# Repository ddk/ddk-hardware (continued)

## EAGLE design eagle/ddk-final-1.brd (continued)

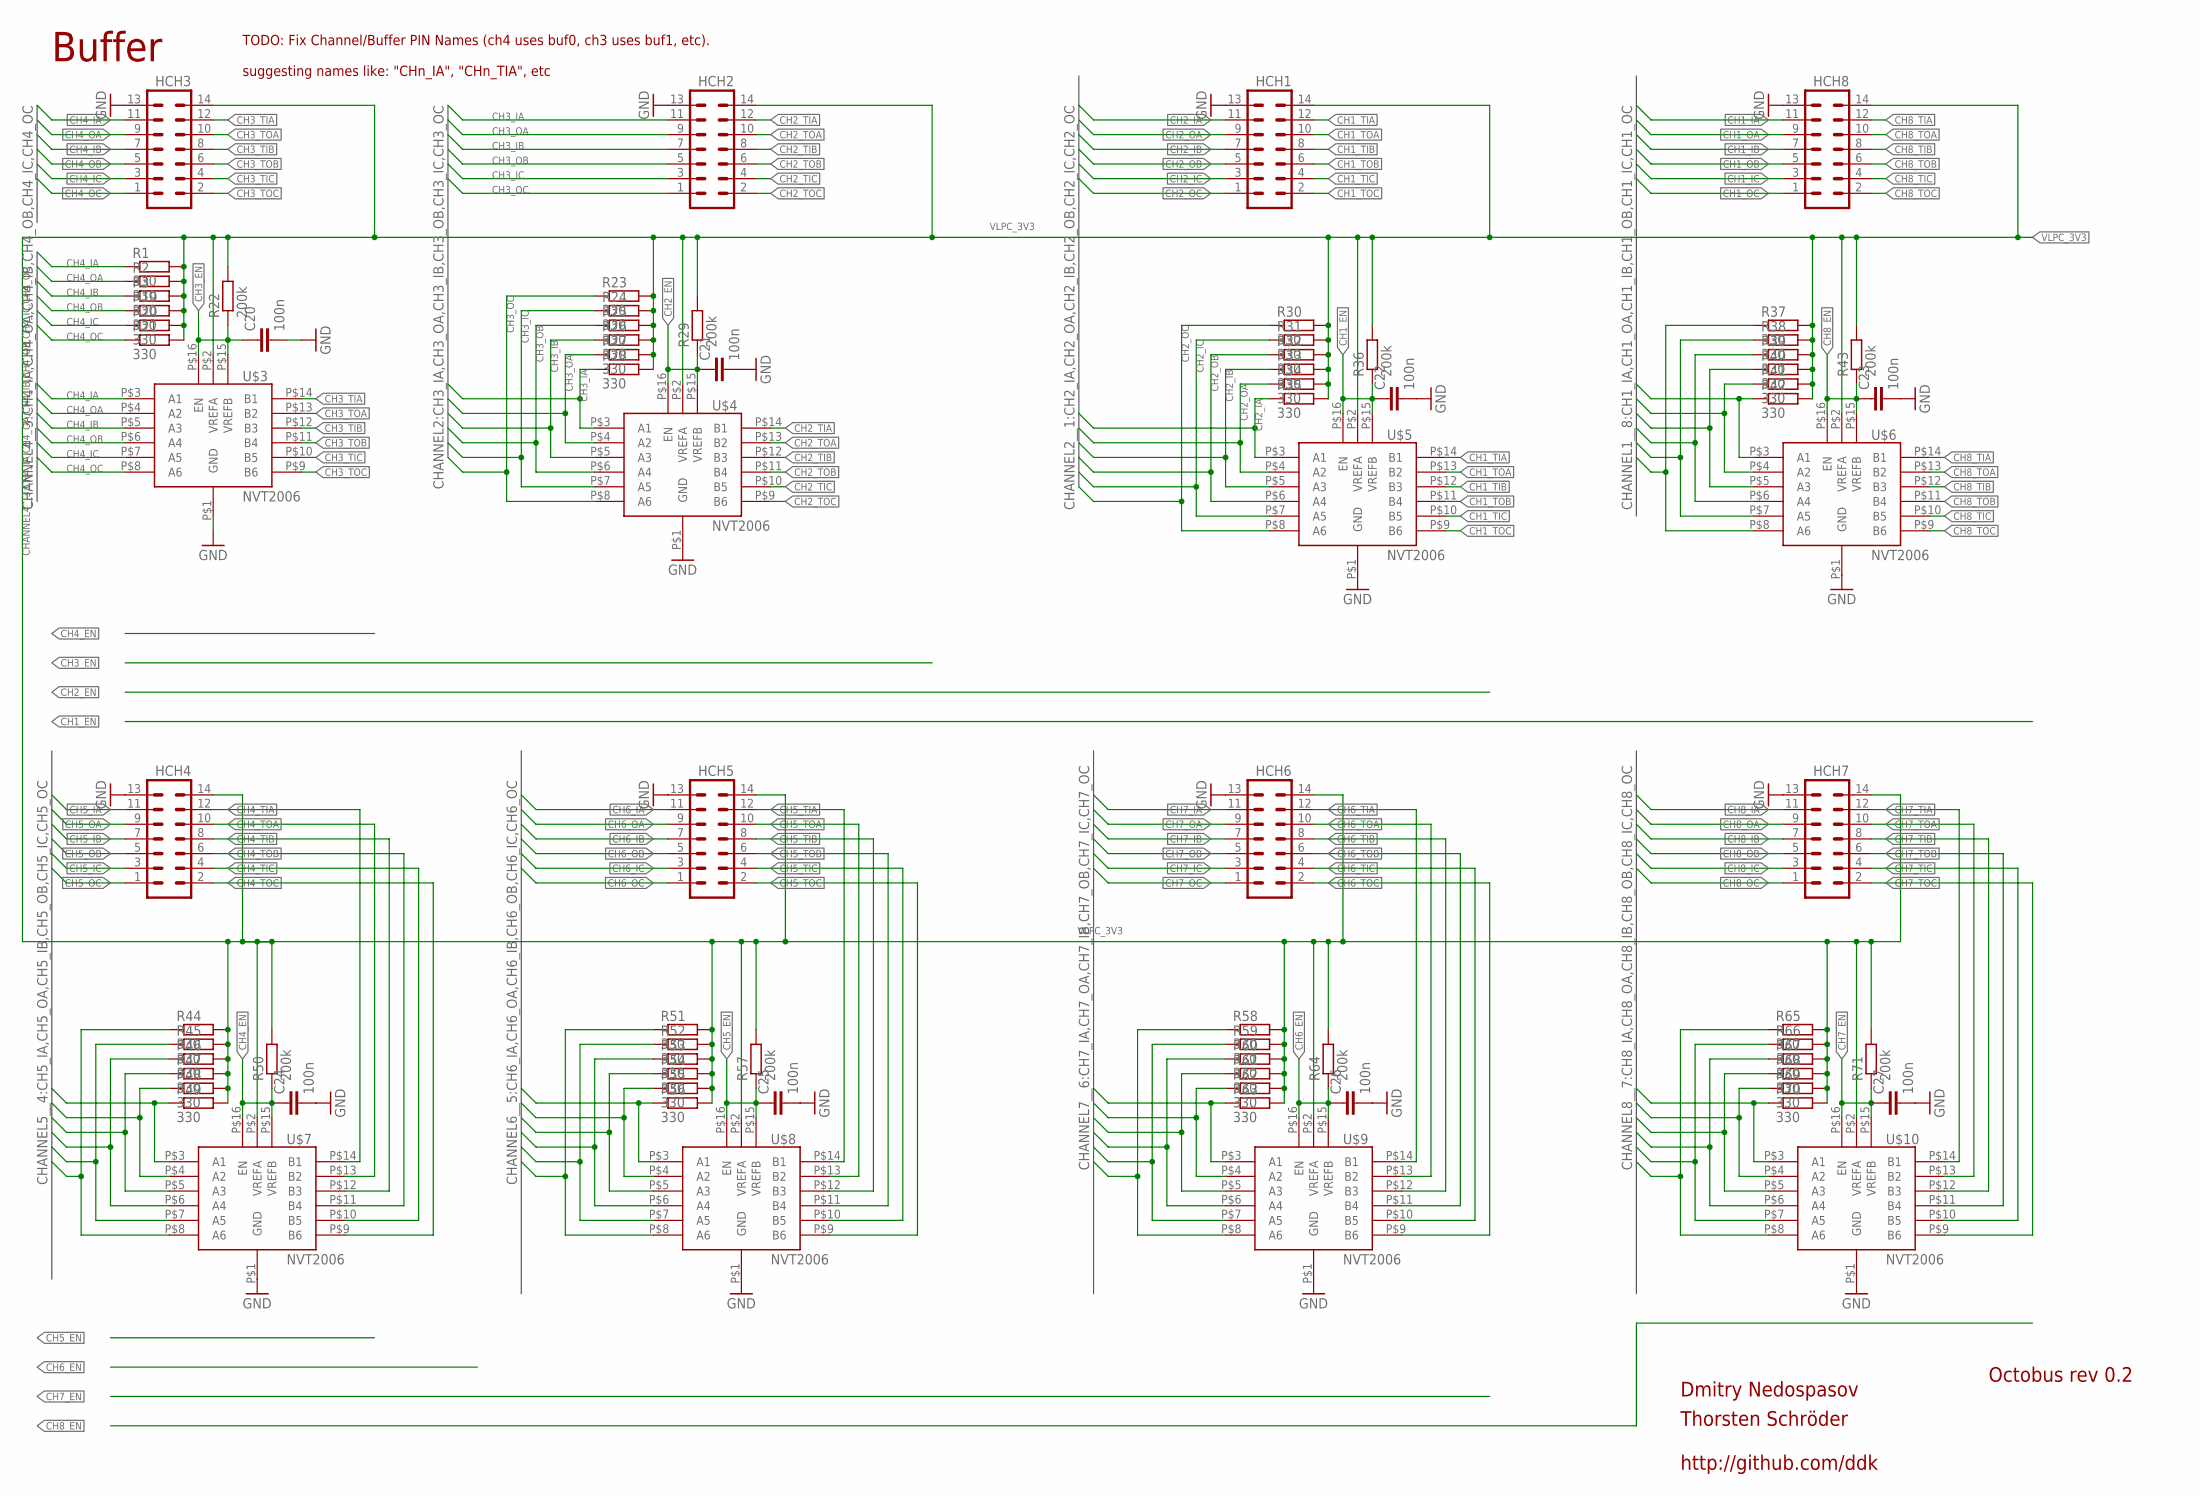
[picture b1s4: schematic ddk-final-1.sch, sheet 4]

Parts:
C20, C21, C22, C23, C24, C25, C26, C27: 100n; C0603
HCH1, HCH2, HCH3, HCH4, HCH5, HCH6, HCH7, HCH8: MA07-2
R1, R2, R3, R19, R20, R21, R23, R24, R25, R26, R27, R28, R30, R31, R32, R33, R34, R35, R37, R38, R39, R40, R41, R42, R44, R45, R46, R47, R48, R49, R51, R52, R53, R54, R55, R56, R58, R59, R60, R61, R62, R63, R65, R66, R67, R68, R69, R70: 330; R0603
R22, R29, R36, R43, R50, R57, R64, R71: 200k; R0603
U$3, U$4, U$5, U$6, U$7, U$8, U$9, U$10: NVT2006; TSSOP16

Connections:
CH1_EN: C22.1, R36.1, U$5.P$15 (VREFB), U$5.P$16 (EN); also elsewhere on the board
CH1_IA: HCH8.11, R42.1, U$6.P$3 (A1); also elsewhere on the board
CH1_IB: HCH8.7, R40.1, U$6.P$5 (A3); also elsewhere on the board
CH1_IC: HCH8.3, R38.1, U$6.P$7 (A5); also elsewhere on the board
CH1_OA: HCH8.9, R41.1, U$6.P$4 (A2); also elsewhere on the board
CH1_OB: HCH8.5, R39.1, U$6.P$6 (A4); also elsewhere on the board
CH1_OC: HCH8.1, R37.1, U$6.P$8 (A6); also elsewhere on the board
CH1_TIA: HCH1.12, U$5.P$14 (B1); also elsewhere on the board
CH1_TIB: HCH1.8, U$5.P$12 (B3); also elsewhere on the board
CH1_TIC: HCH1.4, U$5.P$10 (B5); also elsewhere on the board
CH1_TOA: HCH1.10, U$5.P$13 (B2); also elsewhere on the board
CH1_TOB: HCH1.6, U$5.P$11 (B4); also elsewhere on the board
CH1_TOC: HCH1.2, U$5.P$9 (B6); also elsewhere on the board
CH2_EN: C21.1, R29.1, U$4.P$15 (VREFB), U$4.P$16 (EN); also elsewhere on the board
CH2_IA: HCH1.11, R35.1, U$5.P$3 (A1); also elsewhere on the board
CH2_IB: HCH1.7, R33.1, U$5.P$5 (A3); also elsewhere on the board
CH2_IC: HCH1.3, R31.1, U$5.P$7 (A5); also elsewhere on the board
CH2_OA: HCH1.9, R34.1, U$5.P$4 (A2); also elsewhere on the board
CH2_OB: HCH1.5, R32.1, U$5.P$6 (A4); also elsewhere on the board
CH2_OC: HCH1.1, R30.1, U$5.P$8 (A6); also elsewhere on the board
CH2_TIA: HCH2.12, U$4.P$14 (B1); also elsewhere on the board
CH2_TIB: HCH2.8, U$4.P$12 (B3); also elsewhere on the board
CH2_TIC: HCH2.4, U$4.P$10 (B5); also elsewhere on the board
CH2_TOA: HCH2.10, U$4.P$13 (B2); also elsewhere on the board
CH2_TOB: HCH2.6, U$4.P$11 (B4); also elsewhere on the board
CH2_TOC: HCH2.2, U$4.P$9 (B6); also elsewhere on the board
CH3_EN: C20.1, R22.1, U$3.P$15 (VREFB), U$3.P$16 (EN); also elsewhere on the board
CH3_IA: HCH2.11, R28.1, U$4.P$3 (A1); also elsewhere on the board
CH3_IB: HCH2.7, R26.1, U$4.P$5 (A3); also elsewhere on the board
CH3_IC: HCH2.3, R24.1, U$4.P$7 (A5); also elsewhere on the board
CH3_OA: HCH2.9, R27.1, U$4.P$4 (A2); also elsewhere on the board
CH3_OB: HCH2.5, R25.1, U$4.P$6 (A4); also elsewhere on the board
CH3_OC: HCH2.1, R23.1, U$4.P$8 (A6); also elsewhere on the board
CH3_TIA: HCH3.12, U$3.P$14 (B1); also elsewhere on the board
CH3_TIB: HCH3.8, U$3.P$12 (B3); also elsewhere on the board
CH3_TIC: HCH3.4, U$3.P$10 (B5); also elsewhere on the board
CH3_TOA: HCH3.10, U$3.P$13 (B2); also elsewhere on the board
CH3_TOB: HCH3.6, U$3.P$11 (B4); also elsewhere on the board
CH3_TOC: HCH3.2, U$3.P$9 (B6); also elsewhere on the board
CH4_EN: C24.1, R50.1, U$7.P$15 (VREFB), U$7.P$16 (EN); also elsewhere on the board
CH4_IA: HCH3.11, R1.1, U$3.P$3 (A1); also elsewhere on the board
CH4_IB: HCH3.7, R3.1, U$3.P$5 (A3); also elsewhere on the board
CH4_IC: HCH3.3, R20.1, U$3.P$7 (A5); also elsewhere on the board
CH4_OA: HCH3.9, R2.1, U$3.P$4 (A2); also elsewhere on the board
CH4_OB: HCH3.5, R19.1, U$3.P$6 (A4); also elsewhere on the board
CH4_OC: HCH3.1, R21.1, U$3.P$8 (A6); also elsewhere on the board
CH4_TIA: HCH4.12, U$7.P$14 (B1); also elsewhere on the board
CH4_TIB: HCH4.8, U$7.P$12 (B3); also elsewhere on the board
CH4_TIC: HCH4.4, U$7.P$10 (B5); also elsewhere on the board
CH4_TOA: HCH4.10, U$7.P$13 (B2); also elsewhere on the board
CH4_TOB: HCH4.6, U$7.P$11 (B4); also elsewhere on the board
CH4_TOC: HCH4.2, U$7.P$9 (B6); also elsewhere on the board
CH5_EN: C25.1, R57.1, U$8.P$15 (VREFB), U$8.P$16 (EN); also elsewhere on the board
CH5_IA: HCH4.11, R49.1, U$7.P$3 (A1); also elsewhere on the board
CH5_IB: HCH4.7, R47.1, U$7.P$5 (A3); also elsewhere on the board
CH5_IC: HCH4.3, R45.1, U$7.P$7 (A5); also elsewhere on the board
CH5_OA: HCH4.9, R48.1, U$7.P$4 (A2); also elsewhere on the board
CH5_OB: HCH4.5, R46.1, U$7.P$6 (A4); also elsewhere on the board
CH5_OC: HCH4.1, R44.1, U$7.P$8 (A6); also elsewhere on the board
CH5_TIA: HCH5.12, U$8.P$14 (B1); also elsewhere on the board
CH5_TIB: HCH5.8, U$8.P$12 (B3); also elsewhere on the board
CH5_TIC: HCH5.4, U$8.P$10 (B5); also elsewhere on the board
CH5_TOA: HCH5.10, U$8.P$13 (B2); also elsewhere on the board
CH5_TOB: HCH5.6, U$8.P$11 (B4); also elsewhere on the board
CH5_TOC: HCH5.2, U$8.P$9 (B6); also elsewhere on the board
CH6_EN: C26.1, R64.1, U$9.P$15 (VREFB), U$9.P$16 (EN); also elsewhere on the board
CH6_IA: HCH5.11, R56.1, U$8.P$3 (A1); also elsewhere on the board
CH6_IB: HCH5.7, R54.1, U$8.P$5 (A3); also elsewhere on the board
CH6_IC: HCH5.3, R52.1, U$8.P$7 (A5); also elsewhere on the board
CH6_OA: HCH5.9, R55.1, U$8.P$4 (A2); also elsewhere on the board
CH6_OB: HCH5.5, R53.1, U$8.P$6 (A4); also elsewhere on the board
CH6_OC: HCH5.1, R51.1, U$8.P$8 (A6); also elsewhere on the board
CH6_TIA: HCH6.12, U$9.P$14 (B1); also elsewhere on the board
CH6_TIB: HCH6.8, U$9.P$12 (B3); also elsewhere on the board
CH6_TIC: HCH6.4, U$9.P$10 (B5); also elsewhere on the board
CH6_TOA: HCH6.10, U$9.P$13 (B2); also elsewhere on the board
CH6_TOB: HCH6.6, U$9.P$11 (B4); also elsewhere on the board
CH6_TOC: HCH6.2, U$9.P$9 (B6); also elsewhere on the board
CH7_EN: C27.1, R71.1, U$10.P$15 (VREFB), U$10.P$16 (EN); also elsewhere on the board
CH7_IA: HCH6.11, R63.1, U$9.P$3 (A1); also elsewhere on the board
CH7_IB: HCH6.7, R61.1, U$9.P$5 (A3); also elsewhere on the board
CH7_IC: HCH6.3, R59.1, U$9.P$7 (A5); also elsewhere on the board
CH7_OA: HCH6.9, R62.1, U$9.P$4 (A2); also elsewhere on the board
CH7_OB: HCH6.5, R60.1, U$9.P$6 (A4); also elsewhere on the board
CH7_OC: HCH6.1, R58.1, U$9.P$8 (A6); also elsewhere on the board
CH7_TIA: HCH7.12, U$10.P$14 (B1); also elsewhere on the board
CH7_TIB: HCH7.8, U$10.P$12 (B3); also elsewhere on the board
CH7_TIC: HCH7.4, U$10.P$10 (B5); also elsewhere on the board
CH7_TOA: HCH7.10, U$10.P$13 (B2); also elsewhere on the board
CH7_TOB: HCH7.6, U$10.P$11 (B4); also elsewhere on the board
CH7_TOC: HCH7.2, U$10.P$9 (B6); also elsewhere on the board
CH8_EN: C23.1, R43.1, U$6.P$15 (VREFB), U$6.P$16 (EN); also elsewhere on the board
CH8_IA: HCH7.11, R70.1, U$10.P$3 (A1); also elsewhere on the board
CH8_IB: HCH7.7, R68.1, U$10.P$5 (A3); also elsewhere on the board
CH8_IC: HCH7.3, R66.1, U$10.P$7 (A5); also elsewhere on the board
CH8_OA: HCH7.9, R69.1, U$10.P$4 (A2); also elsewhere on the board
CH8_OB: HCH7.5, R67.1, U$10.P$6 (A4); also elsewhere on the board
CH8_OC: HCH7.1, R65.1, U$10.P$8 (A6); also elsewhere on the board
CH8_TIA: HCH8.12, U$6.P$14 (B1); also elsewhere on the board
CH8_TIB: HCH8.8, U$6.P$12 (B3); also elsewhere on the board
CH8_TIC: HCH8.4, U$6.P$10 (B5); also elsewhere on the board
CH8_TOA: HCH8.10, U$6.P$13 (B2); also elsewhere on the board
CH8_TOB: HCH8.6, U$6.P$11 (B4); also elsewhere on the board
CH8_TOC: HCH8.2, U$6.P$9 (B6); also elsewhere on the board
GND: C20.2, C21.2, C22.2, C23.2, C24.2, C25.2, C26.2, C27.2, HCH1.13, HCH2.13, HCH3.13, HCH4.13, HCH5.13, HCH6.13, HCH7.13, HCH8.13, U$3.P$1 (GND), U$4.P$1 (GND), U$5.P$1 (GND), U$6.P$1 (GND), U$7.P$1 (GND), U$8.P$1 (GND), U$9.P$1 (GND), U$10.P$1 (GND); also elsewhere on the board
VLPC_3V3: HCH1.14, HCH2.14, HCH3.14, HCH4.14, HCH5.14, HCH6.14, HCH7.14, HCH8.14, R1.2, R2.2, R3.2, R19.2, R20.2, R21.2, R22.2, R23.2, R24.2, R25.2, R26.2, R27.2, R28.2, R29.2, R30.2, R31.2, R32.2, R33.2, R34.2, R35.2, R36.2, R37.2, R38.2, R39.2, R40.2, R41.2, R42.2, R43.2, R44.2, R45.2, R46.2, R47.2, R48.2, R49.2, R50.2, R51.2, R52.2, R53.2, R54.2, R55.2, R56.2, R57.2, R58.2, R59.2, R60.2, R61.2, R62.2, R63.2, R64.2, R65.2, R66.2, R67.2, R68.2, R69.2, R70.2, R71.2, U$3.P$2 (VREFA), U$4.P$2 (VREFA), U$5.P$2 (VREFA), U$6.P$2 (VREFA), U$7.P$2 (VREFA), U$8.P$2 (VREFA), U$9.P$2 (VREFA), U$10.P$2 (VREFA); also elsewhere on the board

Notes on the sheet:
Buffer
TODO: Fix Channel/Buffer PIN Names (ch4 uses buf0, ch3 uses buf1, etc). suggesting names like: "CHn_IA", "CHn_TIA", etc

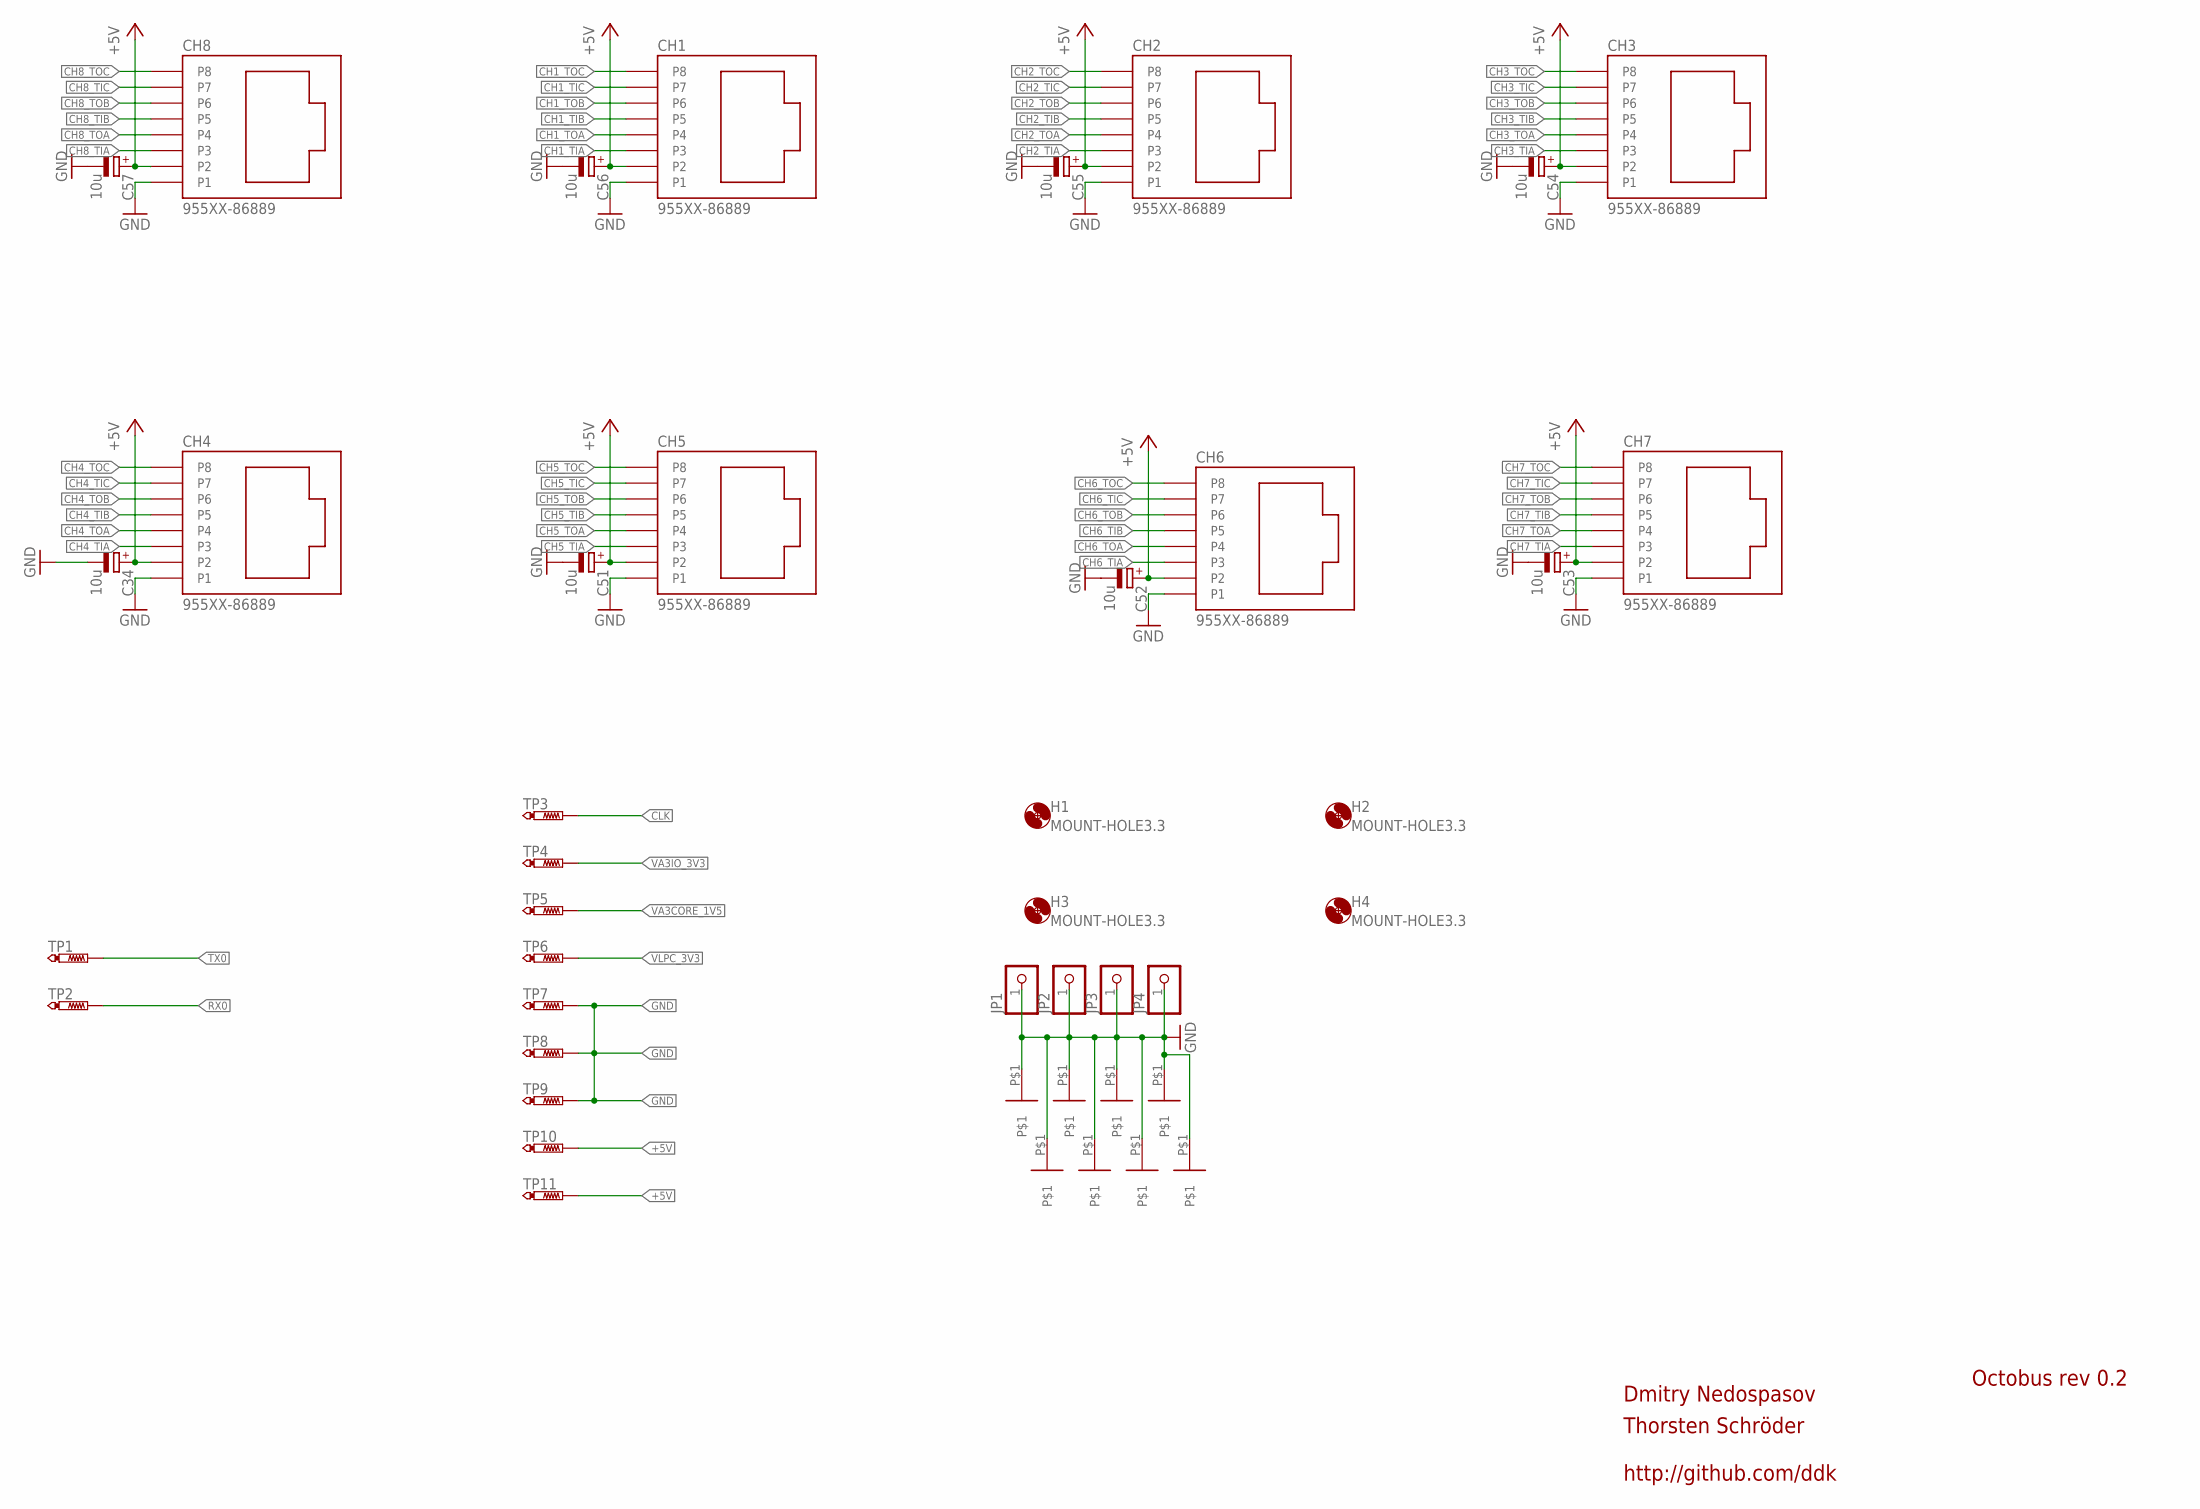
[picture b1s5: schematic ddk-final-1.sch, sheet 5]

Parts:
C34, C51, C52, C53, C54, C55, C56, C57: 10u; CT3216
CH1, CH2, CH3, CH4, CH5, CH6, CH7, CH8: 955XX-86889; 95501
H1, H2, H3, H4: MOUNT-HOLE3.3; 3,3
JP1, JP2, JP3, JP4: PINHD-1X1; 1X01
TP1, TP2, TP4, TP5, TP6, TP7, TP8, TP9, TP10, TP11: PTR1B1,27; B1,27
TP3: PTR1TP08R; TP08R
U$11, U$12, U$13, U$14, U$15, U$16, U$17, U$18: GNDPAD_4MM; GNDPAD

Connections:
+5V: C34.+, C51.+, C52.+, C53.+, C54.+, C55.+, C56.+, C57.+, CH1.P2, CH2.P2, CH3.P2, CH4.P2, CH5.P2, CH6.P2, CH7.P2, CH8.P2, TP10.TP, TP11.TP; also elsewhere on the board
CH1_TIA: CH1.P3; also elsewhere on the board
CH1_TIB: CH1.P5; also elsewhere on the board
CH1_TIC: CH1.P7; also elsewhere on the board
CH1_TOA: CH1.P4; also elsewhere on the board
CH1_TOB: CH1.P6; also elsewhere on the board
CH1_TOC: CH1.P8; also elsewhere on the board
CH2_TIA: CH2.P3; also elsewhere on the board
CH2_TIB: CH2.P5; also elsewhere on the board
CH2_TIC: CH2.P7; also elsewhere on the board
CH2_TOA: CH2.P4; also elsewhere on the board
CH2_TOB: CH2.P6; also elsewhere on the board
CH2_TOC: CH2.P8; also elsewhere on the board
CH3_TIA: CH3.P3; also elsewhere on the board
CH3_TIB: CH3.P5; also elsewhere on the board
CH3_TIC: CH3.P7; also elsewhere on the board
CH3_TOA: CH3.P4; also elsewhere on the board
CH3_TOB: CH3.P6; also elsewhere on the board
CH3_TOC: CH3.P8; also elsewhere on the board
CH4_TIA: CH4.P3; also elsewhere on the board
CH4_TIB: CH4.P5; also elsewhere on the board
CH4_TIC: CH4.P7; also elsewhere on the board
CH4_TOA: CH4.P4; also elsewhere on the board
CH4_TOB: CH4.P6; also elsewhere on the board
CH4_TOC: CH4.P8; also elsewhere on the board
CH5_TIA: CH5.P3; also elsewhere on the board
CH5_TIB: CH5.P5; also elsewhere on the board
CH5_TIC: CH5.P7; also elsewhere on the board
CH5_TOA: CH5.P4; also elsewhere on the board
CH5_TOB: CH5.P6; also elsewhere on the board
CH5_TOC: CH5.P8; also elsewhere on the board
CH6_TIA: CH6.P3; also elsewhere on the board
CH6_TIB: CH6.P5; also elsewhere on the board
CH6_TIC: CH6.P7; also elsewhere on the board
CH6_TOA: CH6.P4; also elsewhere on the board
CH6_TOB: CH6.P6; also elsewhere on the board
CH6_TOC: CH6.P8; also elsewhere on the board
CH7_TIA: CH7.P3; also elsewhere on the board
CH7_TIB: CH7.P5; also elsewhere on the board
CH7_TIC: CH7.P7; also elsewhere on the board
CH7_TOA: CH7.P4; also elsewhere on the board
CH7_TOB: CH7.P6; also elsewhere on the board
CH7_TOC: CH7.P8; also elsewhere on the board
CH8_TIA: CH8.P3; also elsewhere on the board
CH8_TIB: CH8.P5; also elsewhere on the board
CH8_TIC: CH8.P7; also elsewhere on the board
CH8_TOA: CH8.P4; also elsewhere on the board
CH8_TOB: CH8.P6; also elsewhere on the board
CH8_TOC: CH8.P8; also elsewhere on the board
CLK: TP3.TP; also elsewhere on the board
GND: C34.-, C51.-, C52.-, C53.-, C54.-, C55.-, C56.-, C57.-, CH1.P1, CH2.P1, CH3.P1, CH4.P1, CH5.P1, CH6.P1, CH7.P1, CH8.P1, JP1.1, JP2.1, JP3.1, JP4.1, TP7.TP, TP8.TP, TP9.TP, U$11.P$1, U$12.P$1, U$13.P$1, U$14.P$1, U$15.P$1, U$16.P$1, U$17.P$1, U$18.P$1; also elsewhere on the board
RX0: TP2.TP; also elsewhere on the board
TX0: TP1.TP; also elsewhere on the board
VA3CORE_1V5: TP5.TP; also elsewhere on the board
VA3IO_3V3: TP4.TP; also elsewhere on the board
VLPC_3V3: TP6.TP; also elsewhere on the board

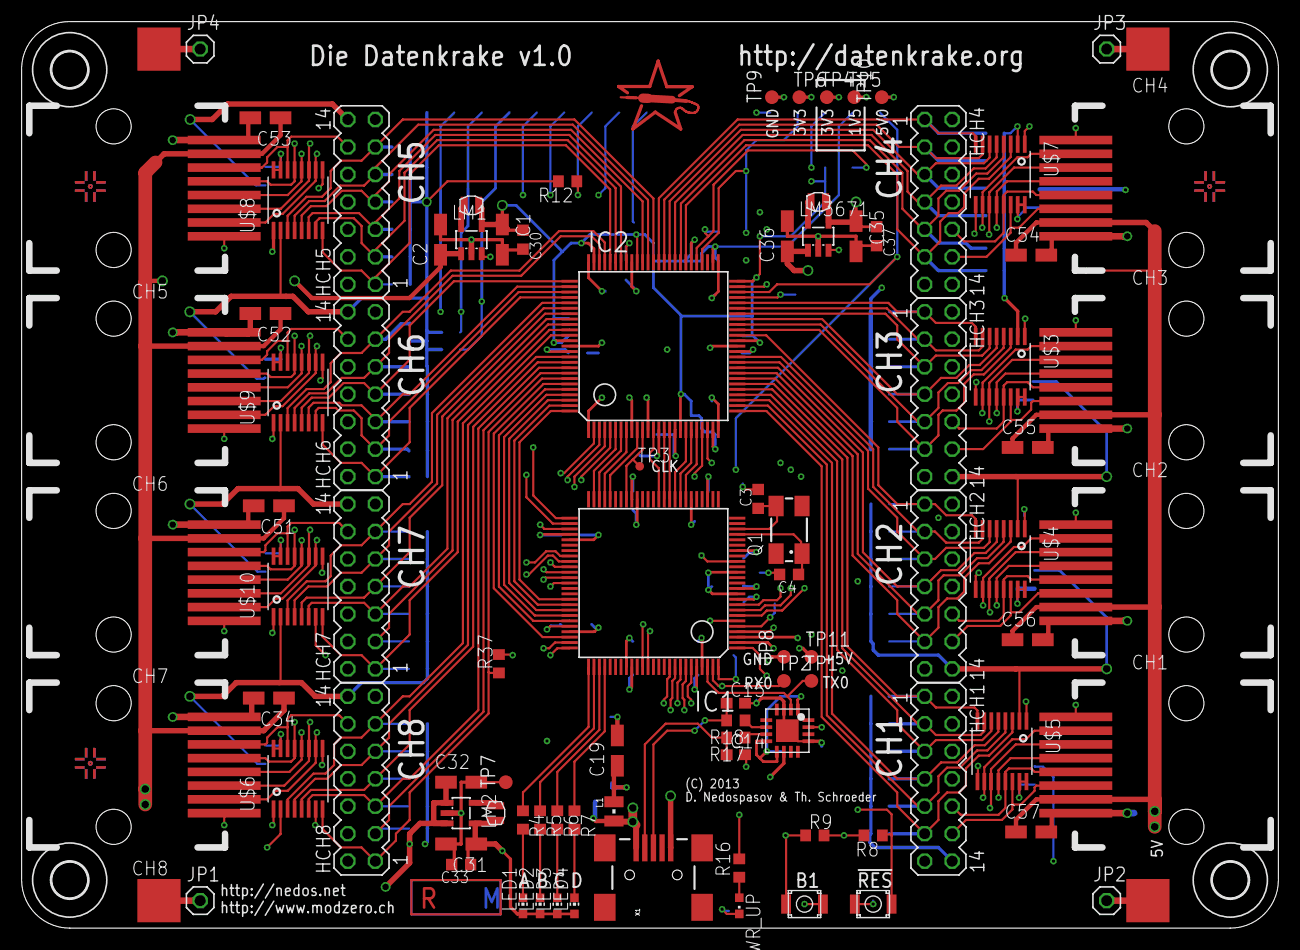
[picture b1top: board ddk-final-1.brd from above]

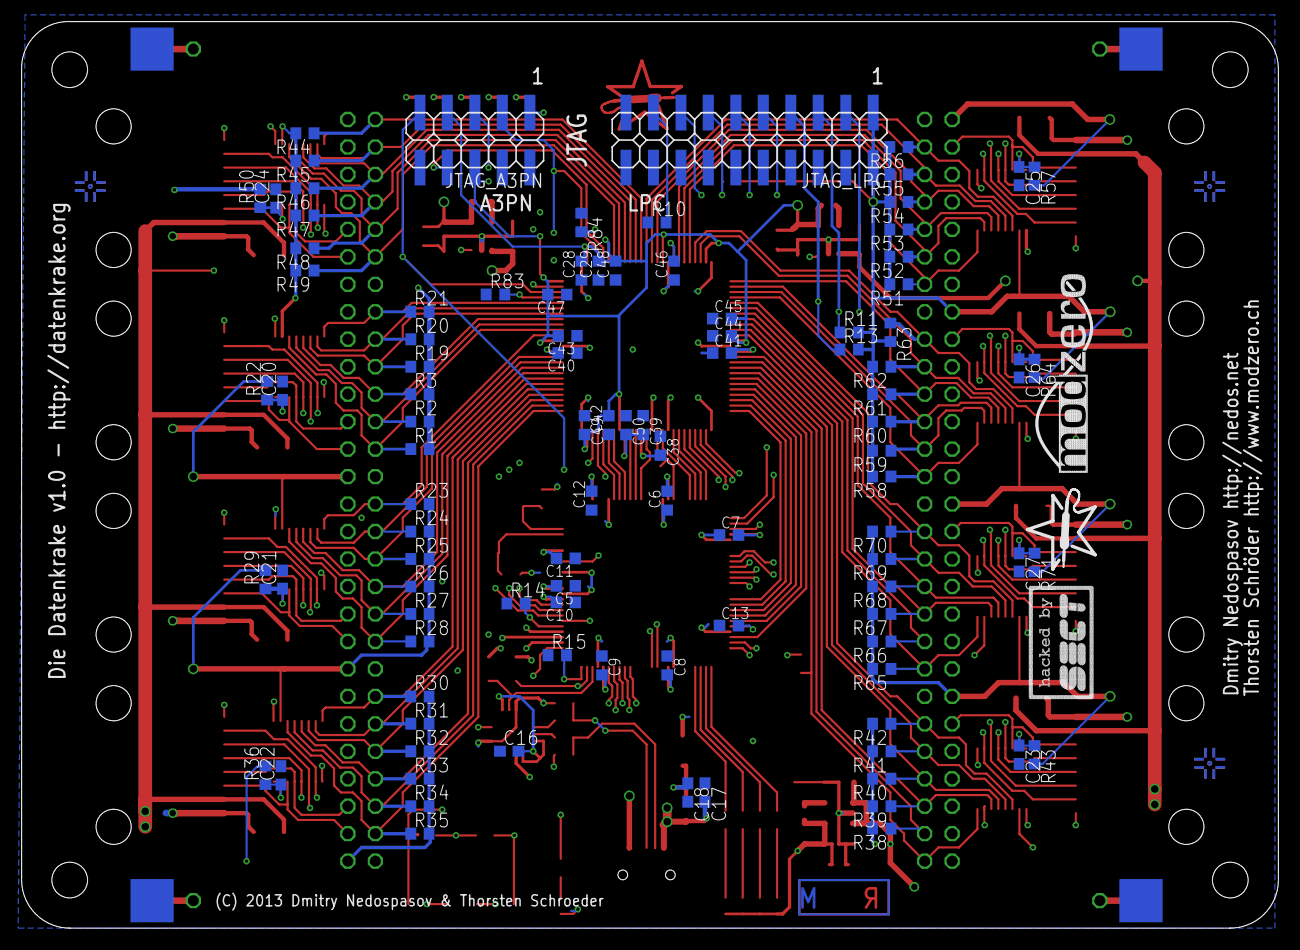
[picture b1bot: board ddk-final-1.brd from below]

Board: 4 copper layers, 116.2 x 83.8 mm, 207 parts (104 on the bottom side), 170 nets.

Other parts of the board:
U$1: LOGO_SMALL
U$19: LOGO_SMALL_TPLACE
U$20, U$21, U$22: PASSER-MARK

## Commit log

2013-06-20 yeah
2013-07-06 Fixed license.
